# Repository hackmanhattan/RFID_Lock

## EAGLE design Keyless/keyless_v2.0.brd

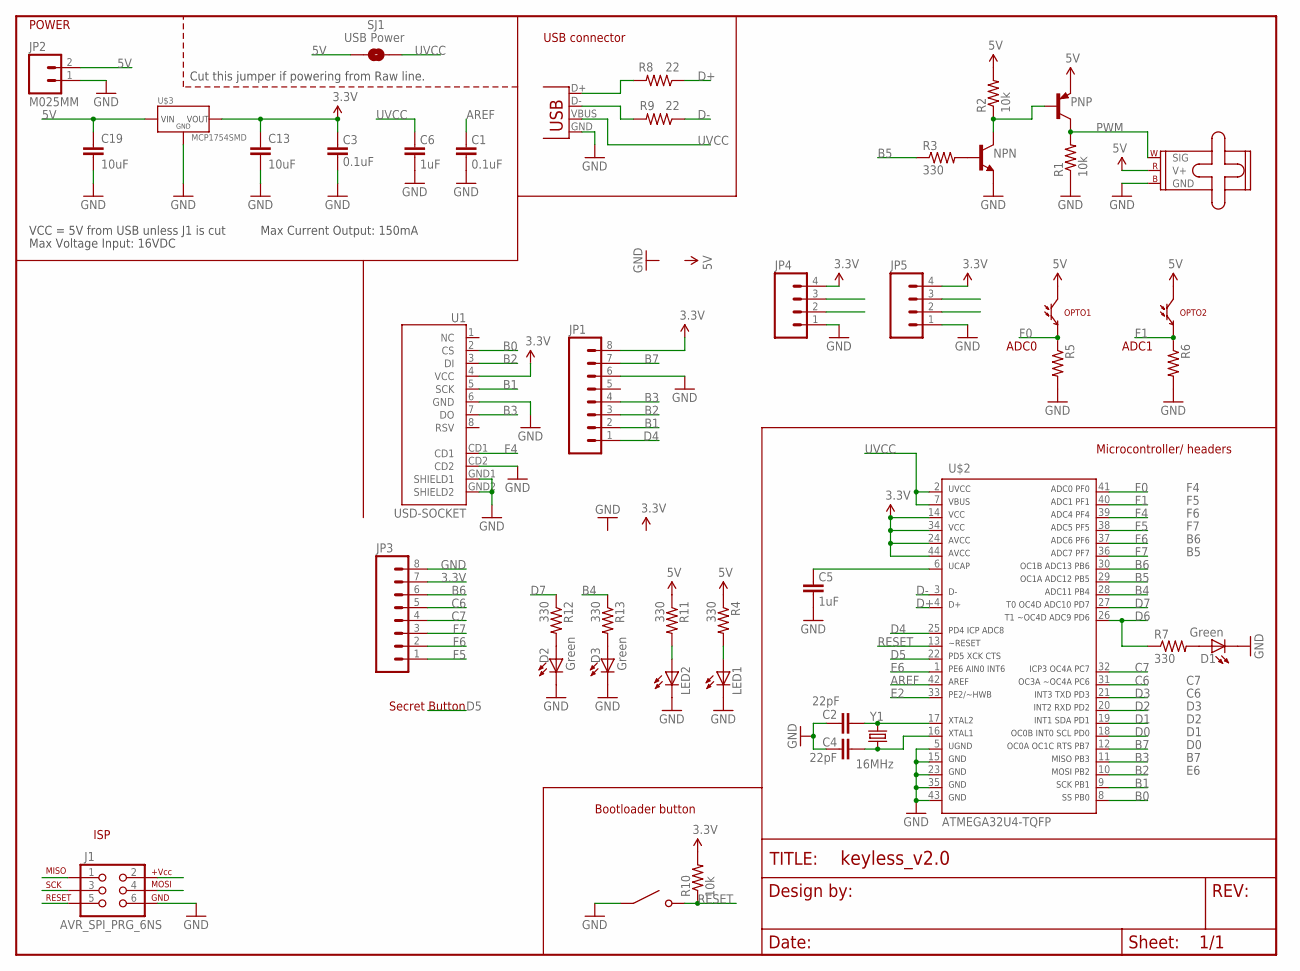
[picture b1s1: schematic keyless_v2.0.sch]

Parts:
C1, C3: 0.1uF; 0603-CAP
C2, C4: 22pF; 0805
C5, C6: 1uF; 0603-CAP
C13, C19: 10uF; C2012
D1, D2, D3: Green; CHIP-LED0805
FRAME1: FRAME-LETTERNONE; NONE
J1: AVR_SPI_PRG_6NS; 2X3-NS
JP1, JP3: M081X08; 1X08
JP2: M025MM; SCREWTERMINAL-5MM-2
JP4, JP5: M04PTH; 1X04
LED1, LED2: LED5MM
NPN: TRANSISTOR_NPNTO-92-AMMO; TO-92-AMMO
OPTO1, OPTO2: LTR-301
PNP: -PNP-TO92-CEB; TO92-CEB
R1, R2: 10k; AXIAL-0.3
R3, R4, R11: 330; AXIAL-0.3
R5, R6: RESISTORAXIAL-0.3; AXIAL-0.3
R7, R12, R13: 330; 0805
R8, R9: 22; 0805
R10: 10k; R0603
SERVO: SMALL_SERVO; 1X03
SJ1: USB Power; SJ_2S-TRACE
U1: USD-SOCKET; USD-SOCKET-DX
U$1: MINI-SPDT; 2-PIN-MINI-PUSHBUTTON
U$2: ATMEGA32U4-TQFP; TQFP44
U$3: MCP1754SMD; SOT23-3
X1: USB-SMD-NS; USB-MINIB-NOHOLE
Y1: 16MHz; ABM2-8X4.5-CRYSTAL

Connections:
3.3V: C3.2, C13.1, J1.2, JP1.8, JP3.7, JP4.4, JP5.4, R10.2, U1.4 (VCC), U$2.14, U$2.24, U$2.34, U$2.44, U$3.2 (VO)
5V: C19.1, JP2.2, OPTO1.C, OPTO2.C, PNP.E, R2.P$2 (2), R4.P$1 (1), R11.P$1 (1), SERVO.2 (V+), SJ1.1, U$3.3 (VCC)
AREF: C1.2, U$2.42
B0: U1.2 (CS), U$2.8
B1: J1.3, JP1.2, U1.5 (SCK), U$2.9
B2: J1.4, JP1.3, U1.3 (DI), U$2.10
B3: J1.1, JP1.4, U1.7 (DO), U$2.11
B4: R13.1, U$2.28
B5: R3.P$1 (1), U$2.29
B6: JP3.6, U$2.30
B7: JP1.7, U$2.12
C6: JP3.5, U$2.31
C7: JP3.4, U$2.32
D0: JP5.2, U$2.18
D1: JP5.3, U$2.19
D2: JP4.2, U$2.20
D3: JP4.3, U$2.21
D4: JP1.1, U$2.25
D5: U$2.22
D6: R7.1, U$2.26
D7: R12.1, U$2.27
D+: R8.1, U$2.4
D-: R9.1, U$2.3
E2: U$2.33
E6: U$2.1
F0: OPTO1.E, R5.P$1 (1), U$2.41
F1: OPTO2.E, R6.P$1 (1), U$2.40
F4: U1.CD1, U$2.39
F5: JP3.1, U$2.38
F6: JP3.2, U$2.37
F7: JP3.3, U$2.36
GND: C1.1, C2.2, C3.1, C4.2, C5.1, C6.1, C13.2, C19.2, D1.C, D2.C, D3.C, J1.6, JP1.6, JP2.1, JP3.8, JP4.1, JP5.1, LED1.K (C), LED2.K (C), NPN.1 (E), R1.P$1 (1), R5.P$2 (2), R6.P$2 (2), SERVO.3 (GND), U1.6 (GND), U1.CD2, U1.GND1 (SHIELD1), U1.GND2 (SHIELD2), U$1.P$1, U$2.5, U$2.15, U$2.23, U$2.35, U$2.43, U$3.1 (GND), X1.GND
unnamed: NPN.3 (C), PNP.B, R2.P$1 (1)
unnamed: LED2.A, R11.P$2 (2)
unnamed: D2.A, R12.2
unnamed: NPN.2 (B), R3.P$2 (2)
unnamed: LED1.A, R4.P$2 (2)
unnamed: C4.1, U$2.16, Y1.P$1 (1)
unnamed: R9.2, X1.D-
unnamed: R8.2, X1.D+
unnamed: D3.A, R13.2
unnamed: C2.1, U$2.17, Y1.P$2 (2)
unnamed: D1.A, R7.2
unnamed: C5.2, U$2.6
PWM: PNP.C, R1.P$2 (2), SERVO.1 (SIG)
RESET: J1.5, R10.1, U$1.P$2, U$2.13
UVCC: C6.2, SJ1.2, U$2.2, U$2.7, X1.VBUS

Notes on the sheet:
Microcontroller/ headers
ADC0
ADC1
ISP
USB connector
Max Voltage Input: 16VDC
Max Current Output: 150mA
VCC = 5V from USB unless J1 is cut
Cut this jumper if powering from Raw line.
POWER
Bootloader button
Secret Button

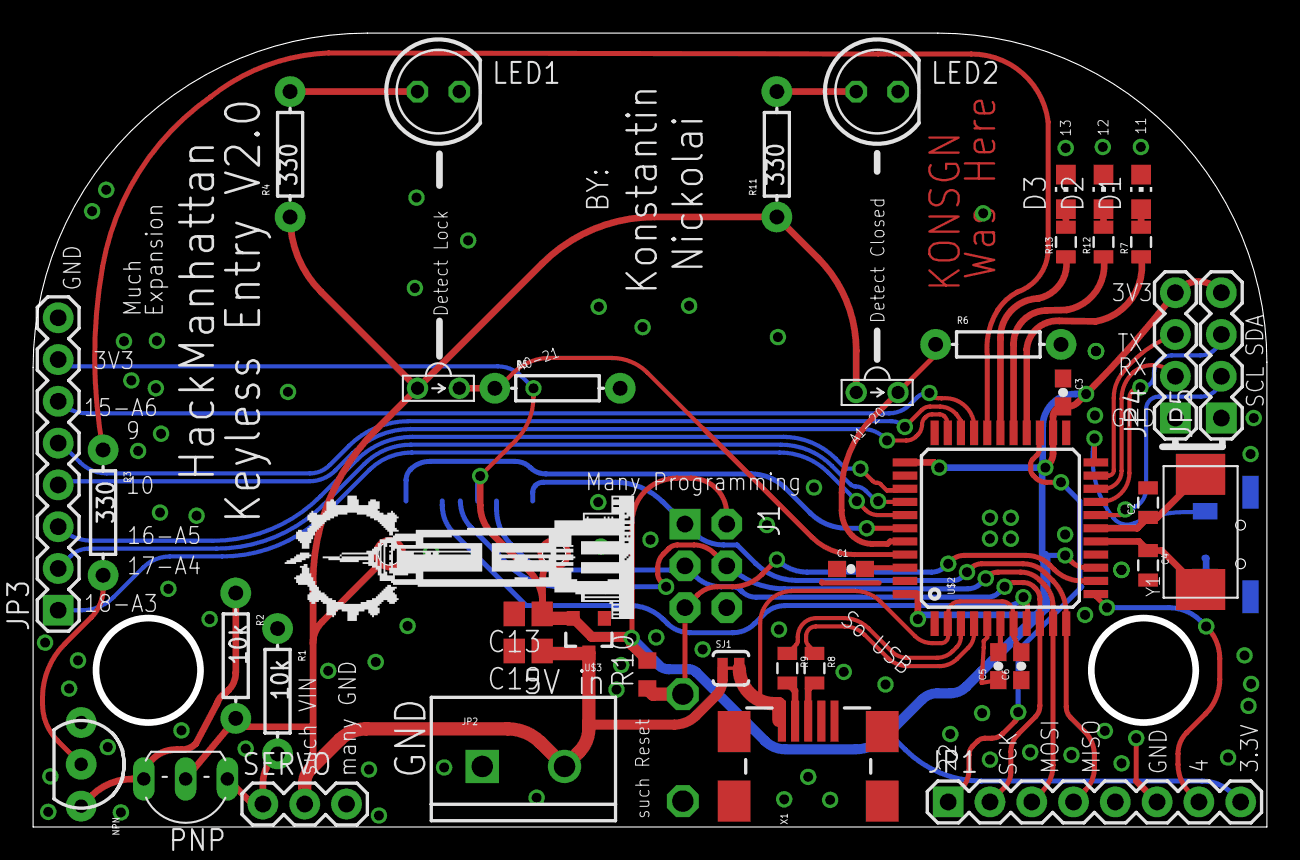
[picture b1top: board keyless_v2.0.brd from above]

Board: 2 copper layers, 75.0 x 48.3 mm, 45 parts (1 on the bottom side), 44 nets.

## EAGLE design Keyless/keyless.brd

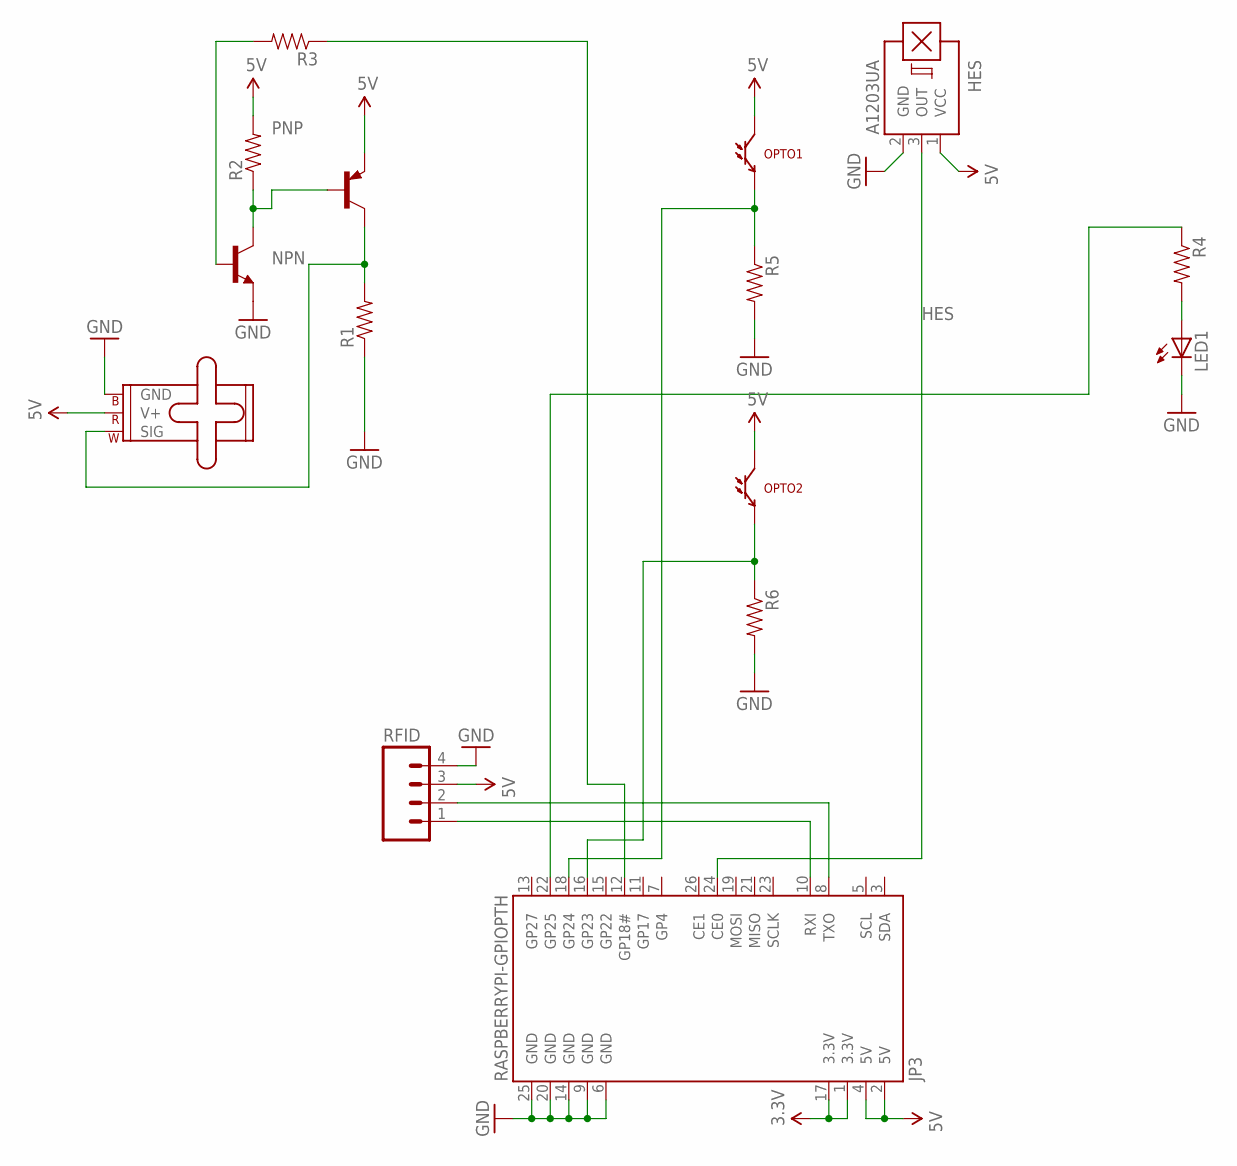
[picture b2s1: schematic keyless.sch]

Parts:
HES: A1203UA; SIP3-UA
JP3: RASPBERRYPI-GPIOPTH; 2X13-SHROUDED
LED1: LED5MM
NPN: TRANSISTOR_NPNTO-92-AMMO; TO-92-AMMO
OPTO1, OPTO2: LTR-301
PNP: -PNP-TO92-CEB; TO92-CEB
R1, R2, R3, R4, R5, R6: RESISTORAXIAL-0.3; AXIAL-0.3
RFID: M04PTH; 1X04
SERVO: SMALL_SERVO; 1X03

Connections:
3.3V: JP3.1 (3.3V), JP3.17 (3.3V)
5V: HES.1 (VCC), JP3.2 (5V), JP3.4 (5V), OPTO1.C, OPTO2.C, PNP.E, R2.P$2 (2), RFID.3, SERVO.2 (V+)
GND: HES.2 (GND), JP3.6 (GND), JP3.9 (GND), JP3.14 (GND), JP3.20 (GND), JP3.25 (GND), LED1.K (C), NPN.1 (E), R1.P$1 (1), R5.P$2 (2), R6.P$2 (2), RFID.4
HES: HES.3 (OUT), JP3.24 (CE0)
unnamed: NPN.3 (C), PNP.B, R2.P$1 (1)
unnamed: JP3.12 (GP18#), R3.P$1 (1)
unnamed: PNP.C, R1.P$2 (2), SERVO.1 (SIG)
unnamed: NPN.2 (B), R3.P$2 (2)
unnamed: LED1.A, R4.P$2 (2)
unnamed: JP3.16 (GP23), OPTO2.E, R6.P$1 (1)
unnamed: JP3.18 (GP24), OPTO1.E, R5.P$1 (1)
unnamed: JP3.10 (RXI), RFID.1
unnamed: JP3.8 (TXO), RFID.2
unnamed: JP3.22 (GP25), R4.P$1 (1)

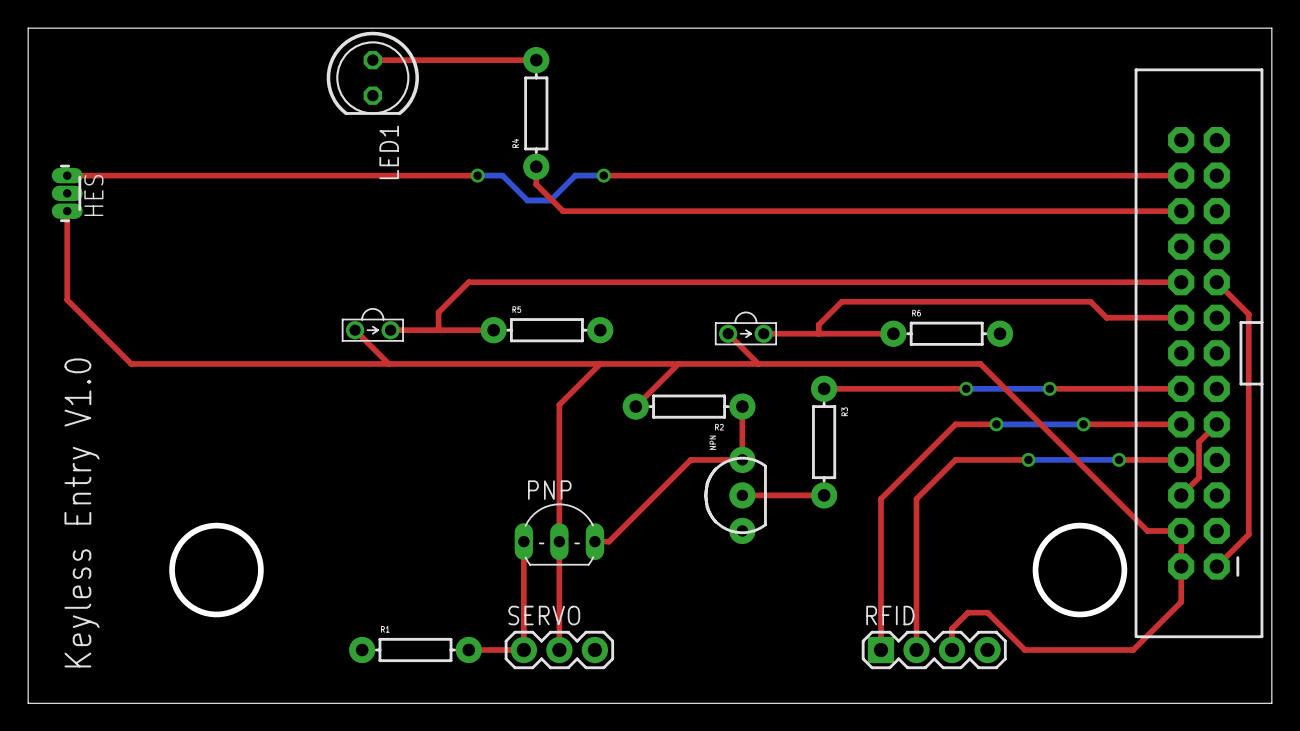
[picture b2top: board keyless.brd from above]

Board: 2 copper layers, 88.9 x 48.3 mm, 15 parts (0 on the bottom side), 14 nets.

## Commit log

2014-04-27 added PCB
2014-04-27 reasons
2014-04-29 more wires!
2014-04-30 more routing!
2014-05-05 more stuffs
2014-05-06 more
2014-05-14 added pin breakouts
2014-05-20 Finalized!
2014-06-03 added values & BOM

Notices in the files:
parts and their libraries:
SparkFun-Connectors: Licensing: CC v3.0 Share-Alike You are welcome to use this library for commercial purposes.
SparkFun-Aesthetics: Released under the Creative Commons Attribution Share-Alike 3.0 License
SparkFun-Aesthetics: http://creativecommons.org/licenses/by-sa/3.0
